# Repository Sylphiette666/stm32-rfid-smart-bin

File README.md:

# STM32与RFID积分式智能移动垃圾桶

嵌入式与RFID双课设的设计和实施资料。当前制作路线为**A1：单台低成本、复用已购模块和直插件，100×100mm裸PCB自行焊接**。主控为STM32F103C8T6，MCP23017成品扩展模块继续外置；一块PCB替代原PWR与IO两块洞洞板，模块按信号名接线。

## 从这里开始

1. [下载图解增强版Word手册](docs/manual/STM32%E4%B8%8ERFID%E6%99%BA%E8%83%BD%E7%A7%BB%E5%8A%A8%E5%9E%83%E5%9C%BE%E6%A1%B6_%E9%80%90%E6%AD%A5%E7%BB%84%E8%A3%85%E4%B8%8E%E8%B0%83%E8%AF%95%E5%AE%9E%E6%96%BD%E6%89%8B%E5%86%8C_%E5%9B%BE%E8%A7%A3%E5%A2%9E%E5%BC%BA%E7%89%88.docx)：保留330个步骤、33项功能；第62章为木板/PVC裁剪图，第63章和图45—49为当前A1 PCB、板外供电、模块接口及条件适配补充。第64章新增四套技能审查结论与接地加强后的调试要求。SG90与历史洞洞板图仍保留。[原版手册](docs/manual/STM32%E4%B8%8ERFID%E6%99%BA%E8%83%BD%E7%A7%BB%E5%8A%A8%E5%9E%83%E5%9C%BE%E6%A1%B6_%E9%80%90%E6%AD%A5%E7%BB%84%E8%A3%85%E4%B8%8E%E8%B0%83%E8%AF%95%E5%AE%9E%E6%96%BD%E6%89%8B%E5%86%8C.docx)保留。
2. [在线阅读全部步骤](docs/manual/ASSEMBLY.md)：按顺序检查、装配和调试，原330步不重编；图解以同名Word最新版为准。
3. [查看当前A1 PCB资料](hardware/current-low-cost/pcb-a/README.md)、[接线说明](hardware/current-low-cost/WIRING.md)、[逐针接口表](hardware/current-low-cost/pcb-a/connector-map.csv)、[BOM](hardware/current-low-cost/pcb-a/manufacturing/bom.csv)和[33项功能验收清单](docs/ACCEPTANCE.md)。裸板制造文件为[Gerber_RS274X.zip](hardware/current-low-cost/pcb-a/manufacturing/Gerber_RS274X.zip)，原理图及工程在[kicad目录](hardware/current-low-cost/pcb-a/kicad/)。
4. [查看SG90等图解与说明](docs/manual/illustrated-additions-20261010/)和[木板与PVC裁剪图解](docs/manual/cutting-diagrams-20261010/)；[旧PWR/IO洞洞板正反面与逐根焊线表](hardware/current-low-cost/perfboard/)仅作归档参考，不再作为A1 PCB施工接口。
5. [打开A1固件与调试说明](firmware/a1/README.md)：开发环境已确定为Keil，编译、下载及调试均在Keil完成，无需安装CubeMX、CubeIDE或CubeProgrammer。已提供工程和烧录文件；先按[实验室集中检查清单](firmware/a1/LAB_CHECKLIST.md)核对硬件，再逐模块上电调试。Word中旧软件路线以此说明和在线手册第37章为准。
6. 当前1号P2S继续昨天第二盘的上平台、舵机支架和喇叭圈。其余四台使用[底座带模块标牌版](hardware/mechanical/print-backup/labeled-bases-20261101/README.md)：两片底板仍可沿用，4/5号两盘精细附件更新为带标牌版，约5小时17分/5小时34分；新增任务同时开打约5小时34分完成，共387g PLA。11个待打印底座加名称，上盖和活动件保持；同名Word66.9节及图解63为当前说明。已切片，未实物试装。

本次接地加强版新增55个GND过孔，不增加元件采购或手焊任务；裸板制造检查通过，仍保留EMC及实物验证边界。详见[四套技能联合审查报告](hardware/current-low-cost/pcb-a/review/four-skills/四套技能联合审查报告.md)。

## 目录

[查看成品外观概念图](docs/appearance/README.md)（合盖与开盖两种状态，非实物照片）。

| 目录 | 内容 |
| --- | --- |
| `docs/manual/` | 原版及最新同名图解增强版Word、330步阅读版、内容源与图解生成源 |
| `docs/manual/illustrated-additions-20261010/` | 本轮SG90等新增图解及整合说明 |
| `docs/manual/cutting-diagrams-20261010/` | 木板/PVC五幅裁剪图、图源、孔位说明及检查记录 |
| `docs/planning/` | 功能成本选型、33项功能机械设计及功能数据 |
| `docs/appearance/` | 成品外观概念图及生成说明 |
| `hardware/mechanical/print-backup/` | PLA整片轻量模型、原5mm厚板备选、P2S打印方向、STEP源和几何检查 |
| `hardware/current-low-cost/` | 当前A1方案的边界、接线说明与归档入口 |
| `hardware/current-low-cost/pcb-a/` | 100×100mm裸PCB、原理图、制造Gerber、BOM和逐针接口表 |
| `hardware/current-low-cost/perfboard/` | 归档：原PWR与IO两块洞洞板正反面、孔位、逐根焊线表及外接说明 |
| `hardware/archive/pcb-v2.1/` | 旧PCF8574方案的嘉立创工程、KiCad、Gerber、BOM和贴片坐标 |
| `firmware/a1/` | A1应用固件、Keil工程、四组主机C测试、发布文件和集中调试说明 |
| `firmware/legacy/` | 保留的STM32/CMSIS基础文件 |
| `archive/` | 较早手册、采购表及折叠内胆参考图 |

## 当前状态与版本边界

- 已整理设计、采购、装配、接线、软件实施步骤和验收方法；文档步骤不代表已完成实物验证。
- 2026-10-13已实现A1应用固件，并通过编译与主机模拟测试；**没有完成实物烧录、标定和整机验收**。默认关闭电机/舵机动作，硬件型号与极性须确认；使用方式见`firmware/a1/README.md`。
- A1继续使用MCP23017成品模块与原MCU功能映射，复用已购器件；AO3400A裸管仍须焊转接板。新PCB只有JP3—JP10共8组跳帽，没有JP1/JP2。旧洞洞板接口及PCF8574 V2.1 PCB均不能混用。
- 当前电气制作基线为2026年10月12日A1 PCB补充；原330步的功能、机械装配和验收顺序保留。PCB的设计检查及制造文件不等于实物焊接、通电或33项功能验收已完成。
- 仓库内没有上传账户凭据、订单截图、渲染缓存、临时锁文件或工具依赖目录。

## 更新方式

后续每次增加图解，都加入同名图解增强版Word，更新目录并渲染检查排版，再替换本地与仓库中的同名版本；同步相关接线说明、图片和校验清单后，提交并推送到本仓库。原330个步骤保持编号。实测记录请写日期、硬件版本、固件提交号、测试条件和结果；未完成检查或实测的项目不能写成已完成。

初始归档日期：2026-10-10。文件校验值见[MANIFEST.sha256](MANIFEST.sha256)。第三方资料说明见[THIRD_PARTY.md](THIRD_PARTY.md)。

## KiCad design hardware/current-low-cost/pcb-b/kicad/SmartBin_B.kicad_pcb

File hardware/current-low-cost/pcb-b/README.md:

# SmartBin B1 模块线束 PCB

本版使用 KiCad，替代面包板和原洞洞板。现有 STM32 核心板、MCP23017、TB6612、降压/稳压板及传感器仍作为独立模块，通过现有排针和按信号标注的杜邦线连接。电池、电机、舵机和 DFPlayer 供电使用接线端子与合适线径，不通过细杜邦线。没有改变现有模块的排针焊接方向。

工程入口：`kicad/SmartBin_B.kicad_pro`；电路板：`kicad/SmartBin_B.kicad_pcb`；完整原理图：`checks/SmartBin_B_schematic.pdf`。B1 与旧 A1 的制造文件不能混用。

`mechanical/SmartBin_B.step` 是用于底座空间检查的PCB装配参考模型，包含KiCad库的名义元件外形；它不是现有独立模块的实测模型。其原点为元件面左上角，STEP中y轴与屏幕向下坐标相反。模型已检查为有效实体。

## 板形与新增电路

- 双层，125×100 mm，1.6 mm 厚，1 oz 铜。正面左上角为坐标原点，x 向右、y 向下。
- 四个 Ø3.2 mm 非金属化安装孔中心：(5,5)、(95,5)、(5,95)、(95,95) mm；孔距仍为 90×90 mm。板右侧比 A1 多出 25 mm，外形不再是 100×100 mm；一体打印底座须按此包络复核，不能按旧草图直接打印。
- 七颗 SN74LVC1G17DBVR（U2—U8，SOT-23-5）处理六路红外 DO 和 DFPlayer BUSY。缓冲器不反相，输入可接 3.3 V 或 5 V 逻辑信号，应用范围限定为共地、0—5.25 V。
- 每路 1 kΩ 输入串联、10 kΩ 上拉、100 nF 就地去耦；电阻和电容为 0805。七颗 IC 加二十一颗 0805 无源器件需要贴片焊接，其余器件以直插为主。
- 接 MCP 的缓冲器由 3V3_EXT 供电；接 PB8、PA12 的两路由 3V3_CORE 供电。两路 3.3 V 不并联。
- 原急停三管电路、AHCT125 输出提升、超声波 Echo 分压、电池 ADC、DHT 适配接口、灯驱动适配接口保留。

## 接口变化

完整逐针接线见 `connector-map.csv`，共 190 个端点。方焊盘为 1 脚；PCB 自定义针序不等于商品模块针序，按模块丝印逐根连接。

| 接口 | B1 接法 |
|---|---|
| J6 | 1=5V_BUS、2=GND，专供 DFPlayer VCC/GND；SPK1/SPK2 只接喇叭 |
| J31 | 1=GND、2=DF_RX、3=DF_BUSY_RAW；BUSY 经 U8 后到 MCP GPA6 |
| J33 | 1=3V3_EXT、2=5V_BUS、3=GND；4—9=IR0_RAW—IR5_RAW |
| J33 信号对应 | 4→GPB0、5→GPB1、6→GPB2、7→GPB3、8→PB8、9→PA12；信号功能沿用 A1 |
| J34 | 三脚均为 GND，分别连接 MCP 的 A0、A1、A2，使地址为 0x20 |
| J35 | 1=3V3_CORE、2=GND；低功耗辅助逻辑口 |
| J36 | 1=3V3_EXT、2=GND；低功耗辅助逻辑口 |
| J37 | 1=5V_BUS、2=GND；低功耗辅助逻辑口 |

J33 上的两种电源是供选择的独立脚，不能同时接到同一模块 VCC。模块 DO 可以进入对应 RAW 输入，不再需要为这七路另搭分压。其余传感器必须遵守各自接口电压，不能把“RAW 支持 5V”推广到所有 GPIO。

外置 AO3400A 转接模块仍接 J28；DHT 双向电平转换成品模块仍接 J23（按选用供电决定 JP8）。这两块应使用已焊好的小模块，不需要面包板。MCP 地址地使用 J34，模块电源按逐针表分配；需要分线时使用绝缘线束分支或现有接线端子。

## 焊接与检查

先焊 U2—U8 和 0805，再焊低矮直插件、排针、端子、电容、U1 插座。U2—U8 的 1 脚对准封装标记；U1 使用 SN74AHCT125N，不用 74HC125 代替。按 BOM 的 DNP 列保留可选电阻空位，不能把所有焊盘全部装满。

断电核查无焊桥、两路 3.3 V 不短接、极性正确。先单独调整降压至 5.0 V，再分阶段接入逻辑和模块；按既有手册确认跳帽供电选择。上拉默认使断线输入为高，感应有效电平和断线行为仍要逐项核对。不同模块断电时不要继续从外部给其信号脚送电。

架空车轮验证急停、释放后不自动续跑，然后再接舵机和负载。原急停只关闭轮电机驱动，并不切断舵机电源；外部 3.3 V 失电时的硬件联锁能力沿用 A1 的限制。本版未实焊、未带载、未做温升或 EMC 验证。

## 校验与制造

`checks/` 保存 ERC、DRC、实际导出网表及 372 个连接管脚/8 个 NC 的逐脚核对。`review/design-audit.json` 核对改动端点、缓冲器原厂引脚、安装孔和原 33 段粗电源线。制造输出只有在最终检查通过后才打包为 `manufacturing/Gerber_RS274X.zip`；BOM 在同目录。

规则：0.20 mm 间距，常规信号 0.30 mm、局部 0.25 mm，过孔 0.8/0.4 mm，原动力主干 3 mm/分支 2 mm保留。低电流缓冲器供电脚采用短 0.30 mm 扇出连接本地去耦，不用于动力供电。双层板的局部回流绕行和原 C8 距离限制仍需实物验证；数字 DRC 通过不等于抗干扰认证。

使用的技能与资料：[mash KiCad skills](https://github.com/mash/kicad-skills)、[PCB-design 检查流程](https://github.com/Toaster496/PCB-design)、[TI SN74LVC1G17 数据手册](https://www.ti.com/lit/ds/symlink/sn74lvc1g17.pdf)。用户已改用 KiCad，本版没有执行 EasyEDA 检查。

## 舵机接线示意图

`diagrams/servo/servo_wiring.png`（同目录另有 A4 横向 `servo_wiring_A4.pdf`）给出 SG90 三根线的分工：红→`J5.1`（5V_BUS，22 AWG，主电流只走这一路）、棕/黑→`J5.2`（GND）、橙→`J20.1`（SERVO_SIG_5V，由 `U1 SN74AHCT125N` 把 PA0 的 3.3 V PWM 提升到 5 V，`R6` 10 kΩ 下拉）。原厂 3 芯延长线必须在配电处拆成电源、信号两路，整根插 `J20` 会把 5 V 灌进信号排针。图源 `diagrams/servo/build_servo_diagram.py`，数据来源与自检见同目录 `diagram-manifest.json`、`diagram-qa.json`（排版自检 0 重叠、导线 0 交叉、像素抽查通过）。该图是接线图，未做实物通电验证。

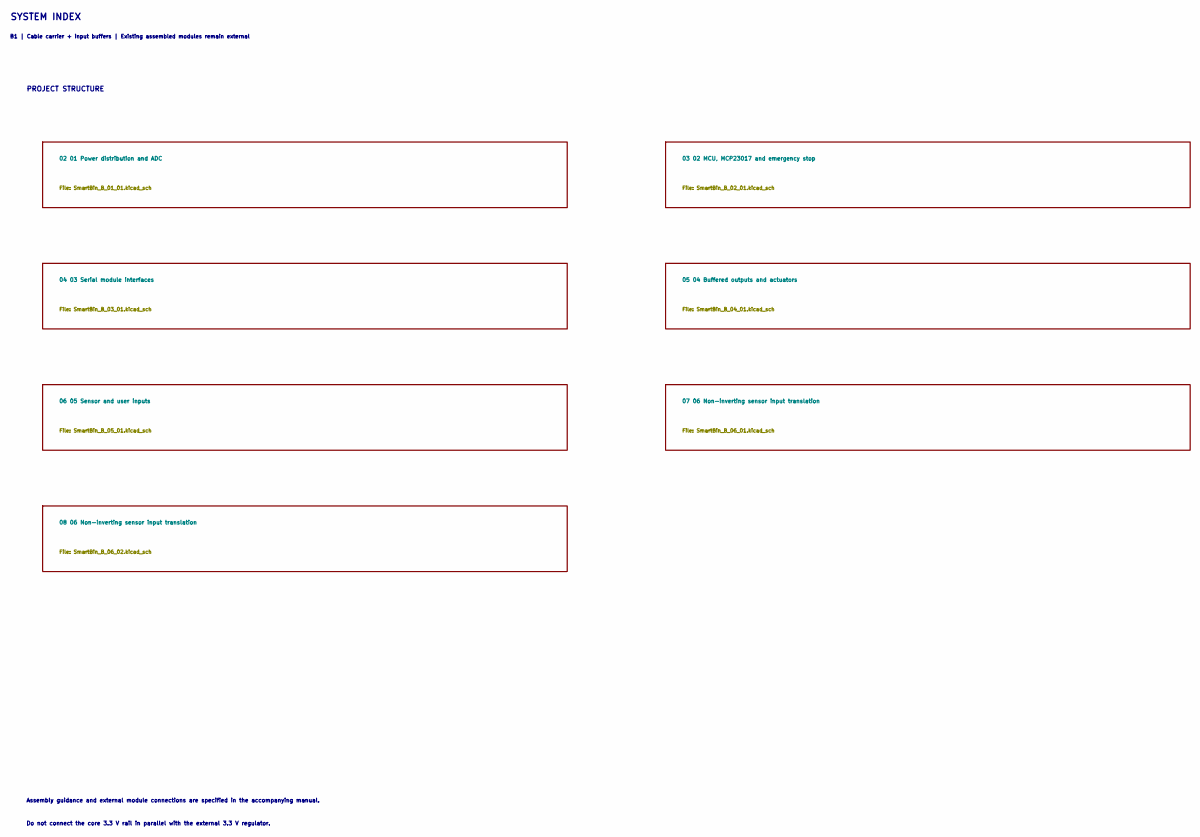
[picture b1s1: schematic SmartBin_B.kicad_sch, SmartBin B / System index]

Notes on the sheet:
SYSTEM INDEX
B1 | Cable carrier + input buffers | Existing assembled modules remain external
PROJECT STRUCTURE
Assembly guidance and external module connections are specified in the accompanying manual.
Do not connect the core 3.3 V rail in parallel with the external 3.3 V regulator.

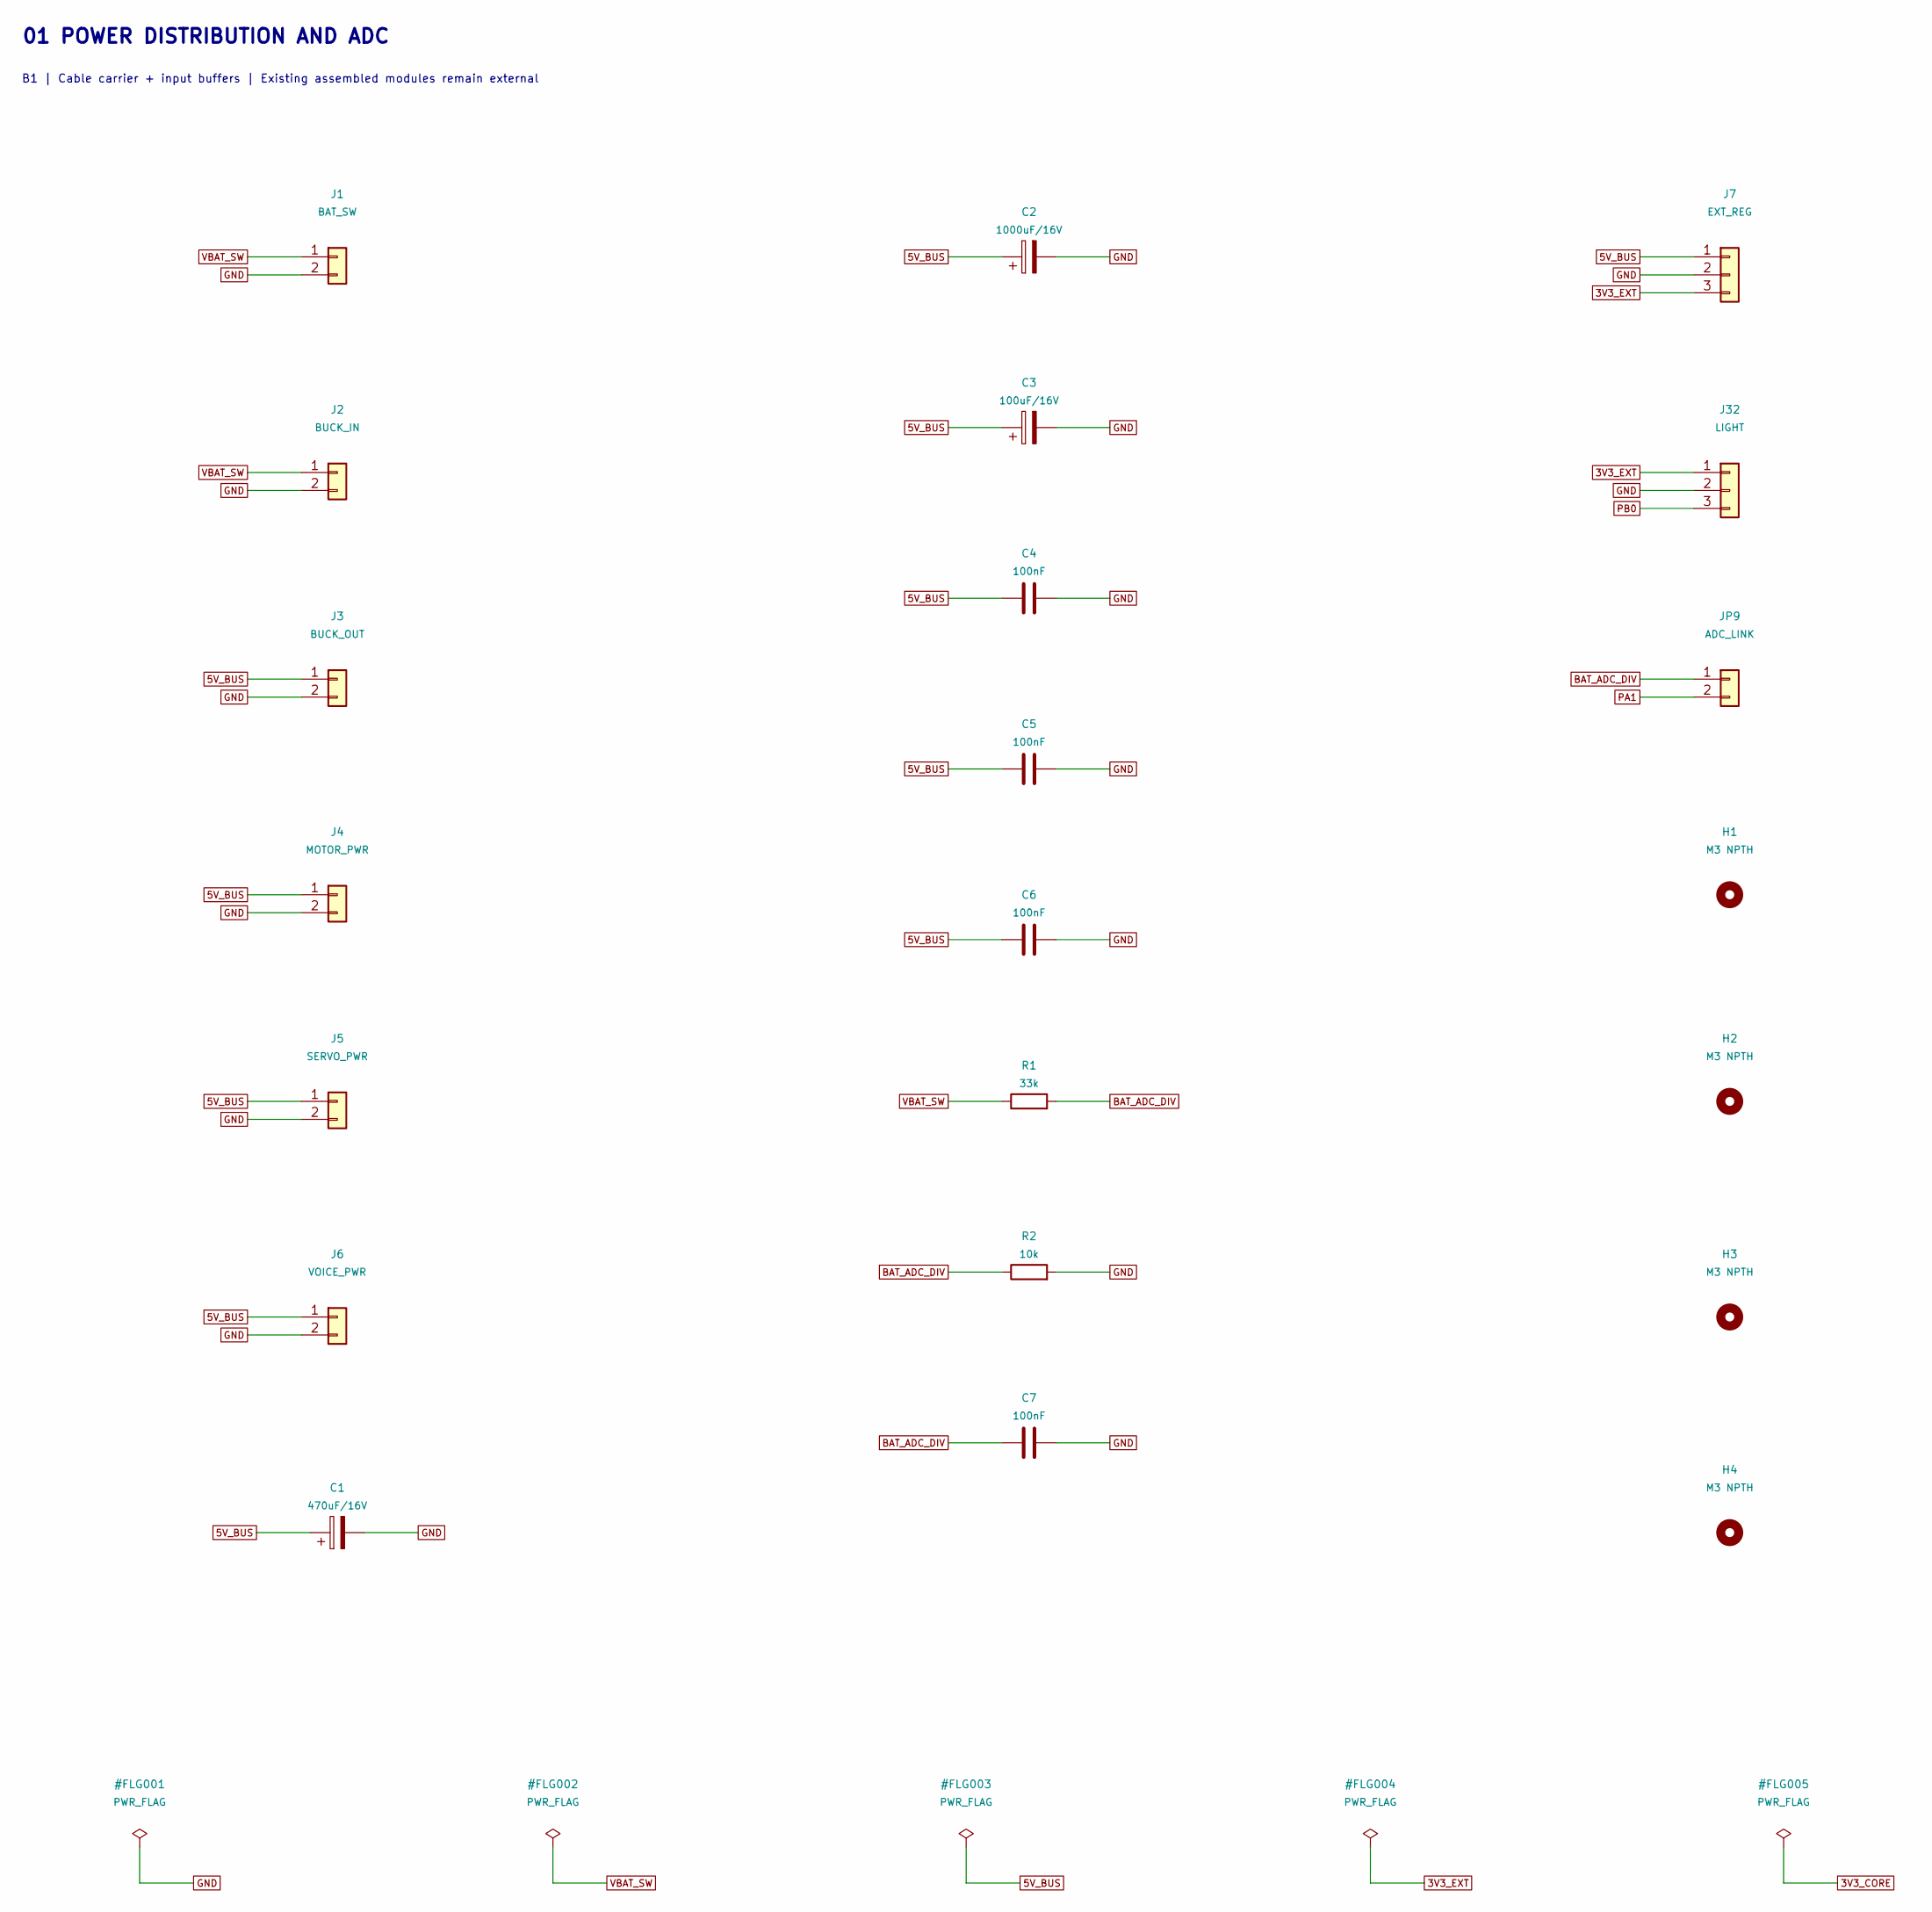
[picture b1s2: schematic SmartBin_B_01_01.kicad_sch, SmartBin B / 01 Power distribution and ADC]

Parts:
C1: 470uF/16V; CP_Radial_D12.5mm_P5.00mm
C2: 1000uF/16V; CP_Radial_D12.5mm_P5.00mm
C3: 100uF/16V; CP_Radial_D12.5mm_P5.00mm
C4, C5, C6, C7: 100nF; C_Disc_D5.0mm_W2.5mm_P5.00mm
H1, H2, H3, H4: M3 NPTH; MountingHole_3.2mm_M3
J1: BAT_SW; TerminalBlock_Phoenix_MKDS-1,5-2-5.08_1x02_P5.08mm_Horizont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
J2: BUCK_IN; TerminalBlock_Phoenix_MKDS-1,5-2-5.08_1x02_P5.08mm_Horizont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
J3: BUCK_OUT; TerminalBlock_Phoenix_MKDS-1,5-2-5.08_1x02_P5.08mm_Horizont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
J4: MOTOR_PWR; TerminalBlock_Phoenix_MKDS-1,5-2-5.08_1x02_P5.08mm_Horizont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
J5: SERVO_PWR; TerminalBlock_Phoenix_MKDS-1,5-2-5.08_1x02_P5.08mm_Horizont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
J6: VOICE_PWR; TerminalBlock_Phoenix_MKDS-1,5-2-5.08_1x02_P5.08mm_Horizont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
J7: EXT_REG; PinHeader_1x03_P2.54mm_Vertical
J32: LIGHT; PinHeader_1x03_P2.54mm_Vertical
JP9: ADC_LINK; PinHeader_1x02_P2.54mm_Vertical
R1: 33k; R_Axial_DIN0207_L6.3mm_D2.5mm_P10.16mm_Horizontal
R2: 10k; R_Axial_DIN0207_L6.3mm_D2.5mm_P10.16mm_Horizontal

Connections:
3V3_EXT: J7.3, J32.1; also elsewhere on the board
5V_BUS: C1.1, C2.1, C3.1, C4.1, C5.1, C6.1, J3.1, J4.1, J5.1, J6.1, J7.1; also elsewhere on the board
BAT_ADC_DIV: C7.1, JP9.1, R1.2, R2.1
GND: C1.2, C2.2, C3.2, C4.2, C5.2, C6.2, C7.2, J1.2, J2.2, J3.2, J4.2, J5.2, J6.2, J7.2, J32.2, R2.2; also elsewhere on the board
PA1: JP9.2; also elsewhere on the board
PB0: J32.3; also elsewhere on the board
VBAT_SW: J1.1, J2.1, R1.1; also elsewhere on the board

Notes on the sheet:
01 POWER DISTRIBUTION AND ADC
B1 | Cable carrier + input buffers | Existing assembled modules remain external

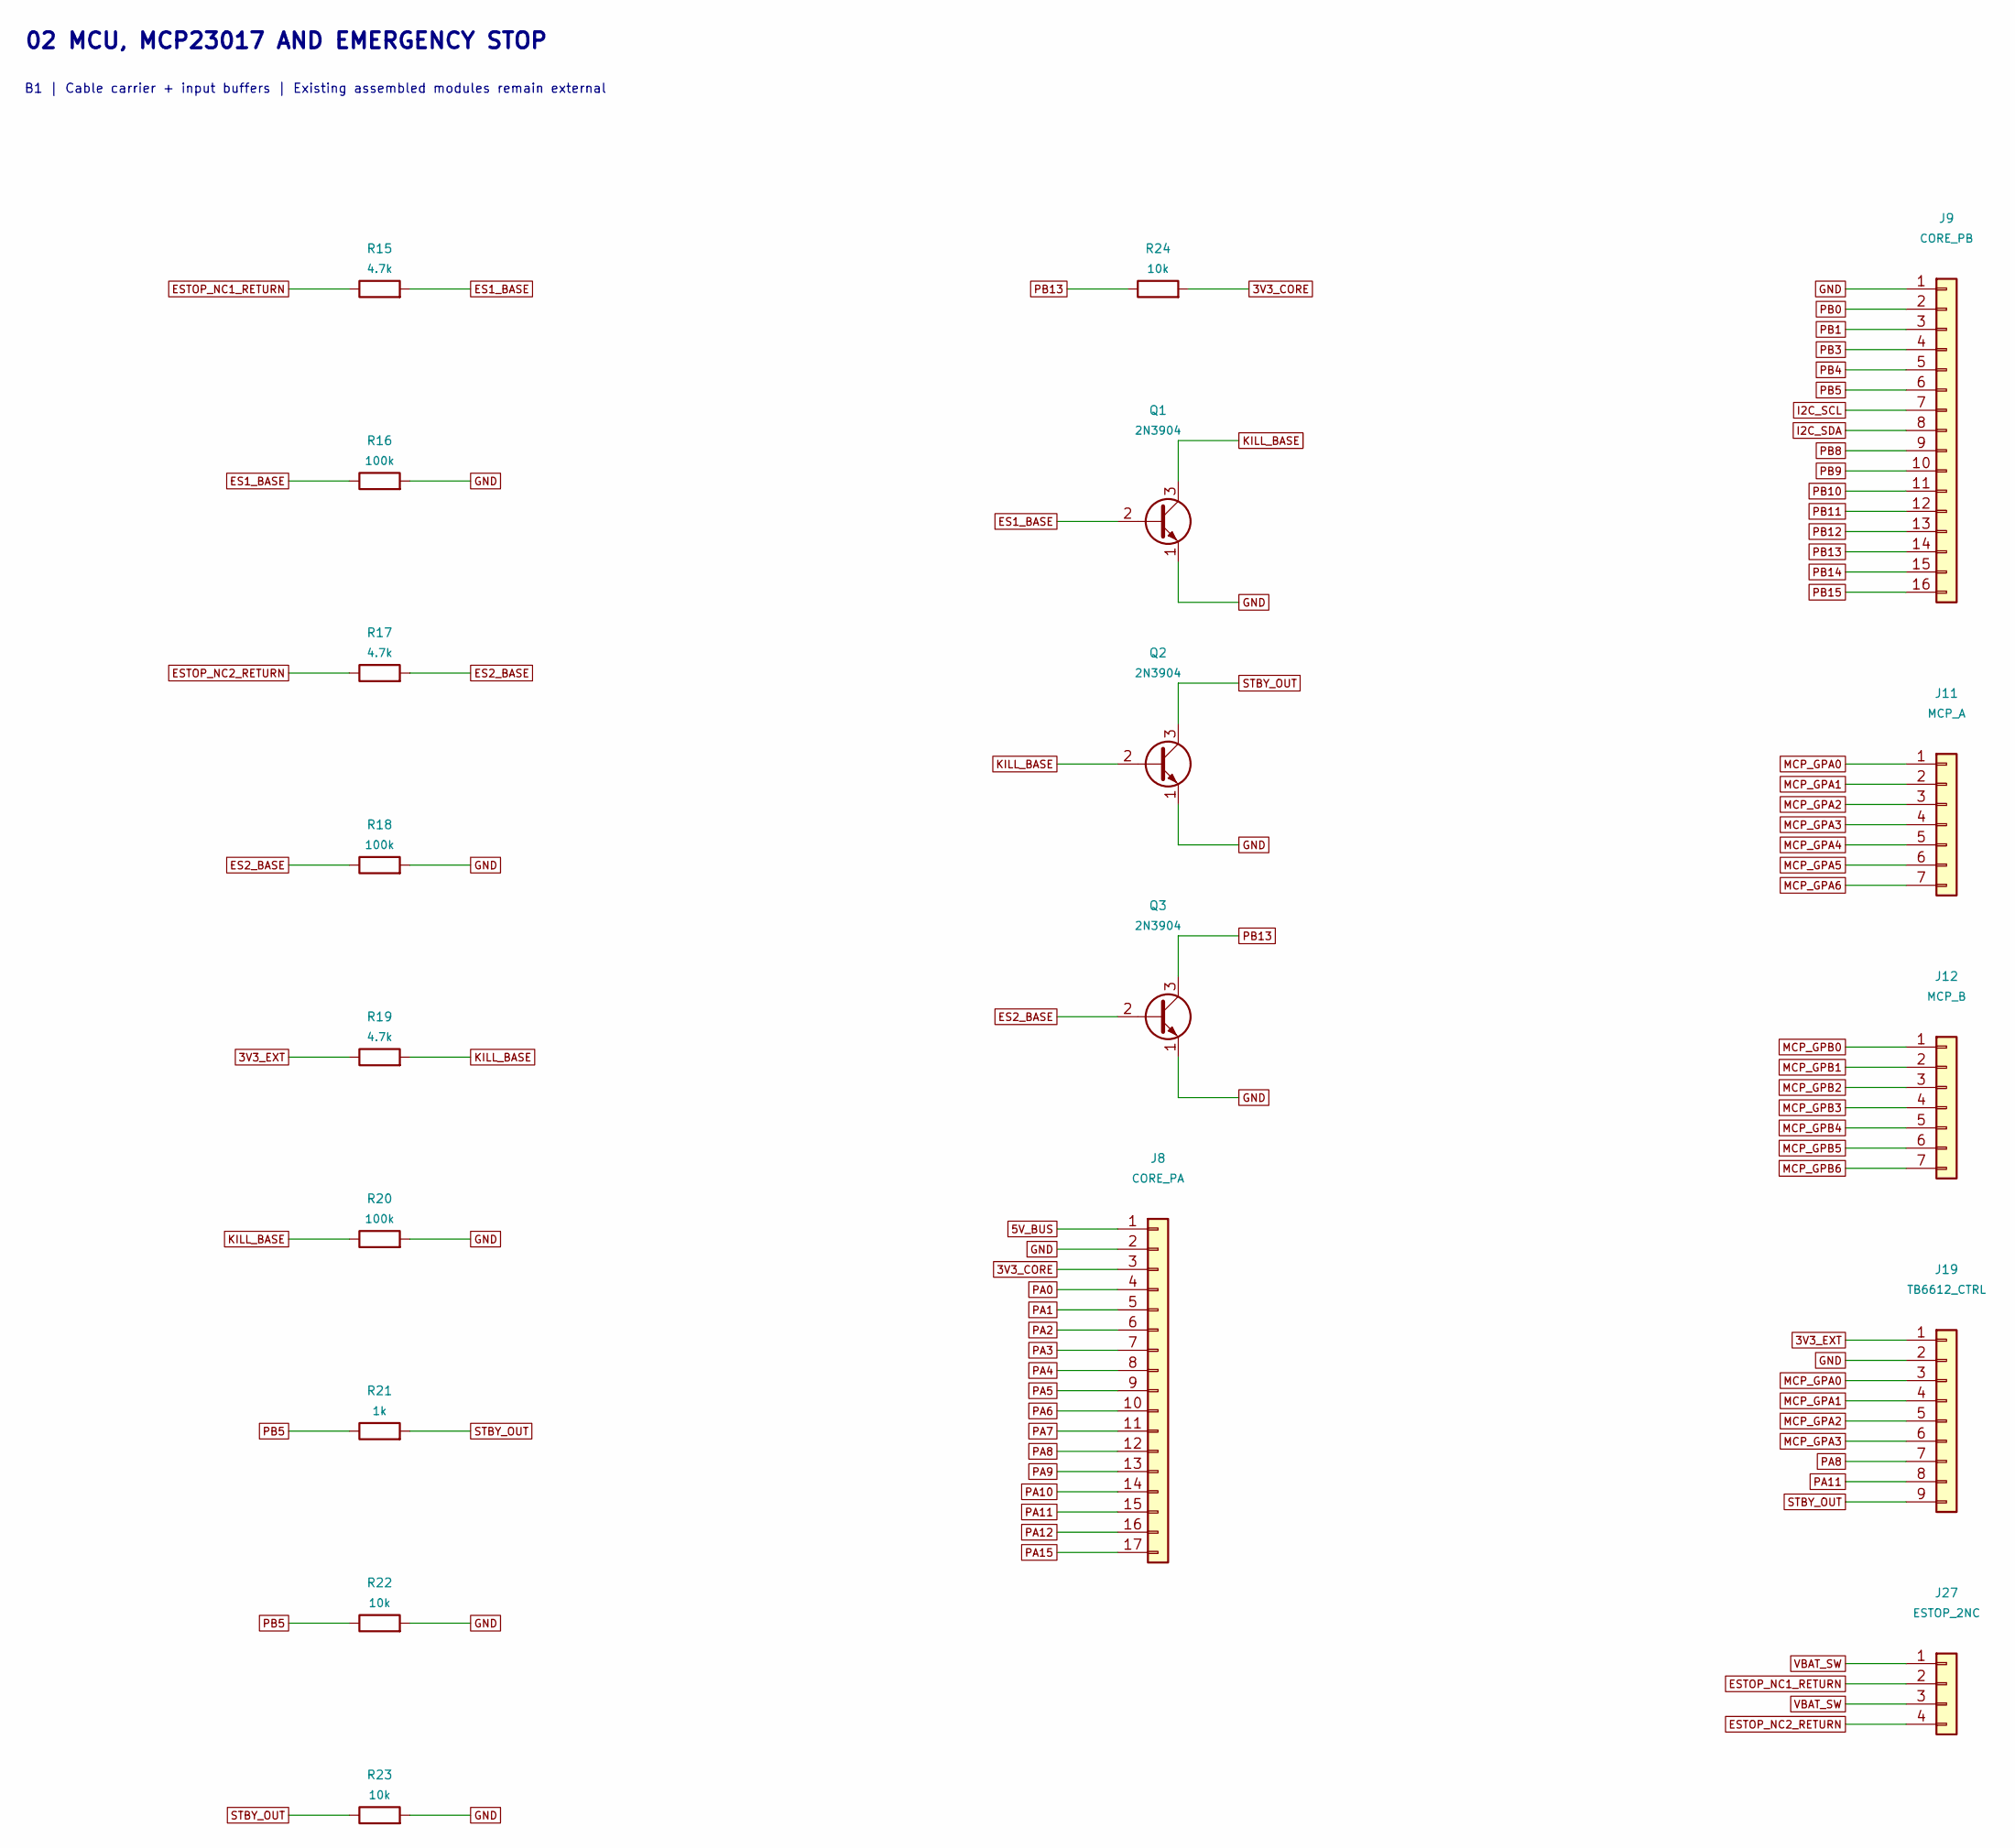
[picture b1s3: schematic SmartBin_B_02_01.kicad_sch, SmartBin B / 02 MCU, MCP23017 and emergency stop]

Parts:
J8: CORE_PA; PinHeader_1x17_P2.54mm_Vertical
J9: CORE_PB; PinHeader_1x16_P2.54mm_Vertical
J11: MCP_A; PinHeader_1x07_P2.54mm_Vertical
J12: MCP_B; PinHeader_1x07_P2.54mm_Vertical
J19: TB6612_CTRL; PinHeader_1x09_P2.54mm_Vertical
J27: ESTOP_2NC; PinHeader_1x04_P2.54mm_Vertical
Q1, Q2, Q3: 2N3904; TO-92_Inline_Wide
R15, R17, R19: 4.7k; R_Axial_DIN0207_L6.3mm_D2.5mm_P10.16mm_Horizontal
R16, R18, R20: 100k; R_Axial_DIN0207_L6.3mm_D2.5mm_P10.16mm_Horizontal
R21: 1k; R_Axial_DIN0207_L6.3mm_D2.5mm_P10.16mm_Horizontal
R22, R23, R24: 10k; R_Axial_DIN0207_L6.3mm_D2.5mm_P10.16mm_Horizontal

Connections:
3V3_CORE: J8.3, R24.2; also elsewhere on the board
3V3_EXT: J19.1, R19.1; also elsewhere on the board
5V_BUS: J8.1; also elsewhere on the board
ES1_BASE: Q1.2 (B), R15.2, R16.1
ES2_BASE: Q3.2 (B), R17.2, R18.1
ESTOP_NC1_RETURN: J27.2, R15.1
ESTOP_NC2_RETURN: J27.4, R17.1
GND: J8.2, J9.1, J19.2, Q1.1 (E), Q2.1 (E), Q3.1 (E), R16.2, R18.2, R20.2, R22.2, R23.2; also elsewhere on the board
I2C_SCL: J9.7; also elsewhere on the board
I2C_SDA: J9.8; also elsewhere on the board
KILL_BASE: Q1.3 (C), Q2.2 (B), R19.2, R20.1
MCP_GPA0: J11.1, J19.3
MCP_GPA1: J11.2, J19.4
MCP_GPA2: J11.3, J19.5
MCP_GPA3: J11.4, J19.6
MCP_GPA4: J11.5; also elsewhere on the board
MCP_GPA5: J11.6; also elsewhere on the board
MCP_GPA6: J11.7; also elsewhere on the board
MCP_GPB0: J12.1; also elsewhere on the board
MCP_GPB1: J12.2; also elsewhere on the board
MCP_GPB2: J12.3; also elsewhere on the board
MCP_GPB3: J12.4; also elsewhere on the board
MCP_GPB4: J12.5; also elsewhere on the board
MCP_GPB5: J12.6; also elsewhere on the board
MCP_GPB6: J12.7; also elsewhere on the board
PA0: J8.4; also elsewhere on the board
PA1: J8.5; also elsewhere on the board
PA2: J8.6; also elsewhere on the board
PA3: J8.7; also elsewhere on the board
PA4: J8.8; also elsewhere on the board
PA5: J8.9; also elsewhere on the board
PA6: J8.10; also elsewhere on the board
PA7: J8.11; also elsewhere on the board
PA8: J8.12, J19.7
PA9: J8.13; also elsewhere on the board
PA10: J8.14; also elsewhere on the board
PA11: J8.15, J19.8
PA12: J8.16; also elsewhere on the board
PA15: J8.17; also elsewhere on the board
PB0: J9.2; also elsewhere on the board
PB1: J9.3; also elsewhere on the board
PB3: J9.4; also elsewhere on the board
PB4: J9.5; also elsewhere on the board
PB5: J9.6, R21.1, R22.1
PB8: J9.9; also elsewhere on the board
PB9: J9.10; also elsewhere on the board
PB10: J9.11; also elsewhere on the board
PB11: J9.12; also elsewhere on the board
PB12: J9.13; also elsewhere on the board
PB13: J9.14, Q3.3 (C), R24.1
PB14: J9.15; also elsewhere on the board
PB15: J9.16; also elsewhere on the board
STBY_OUT: J19.9, Q2.3 (C), R21.2, R23.1
VBAT_SW: J27.1, J27.3; also elsewhere on the board

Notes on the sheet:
02 MCU, MCP23017 AND EMERGENCY STOP
B1 | Cable carrier + input buffers | Existing assembled modules remain external

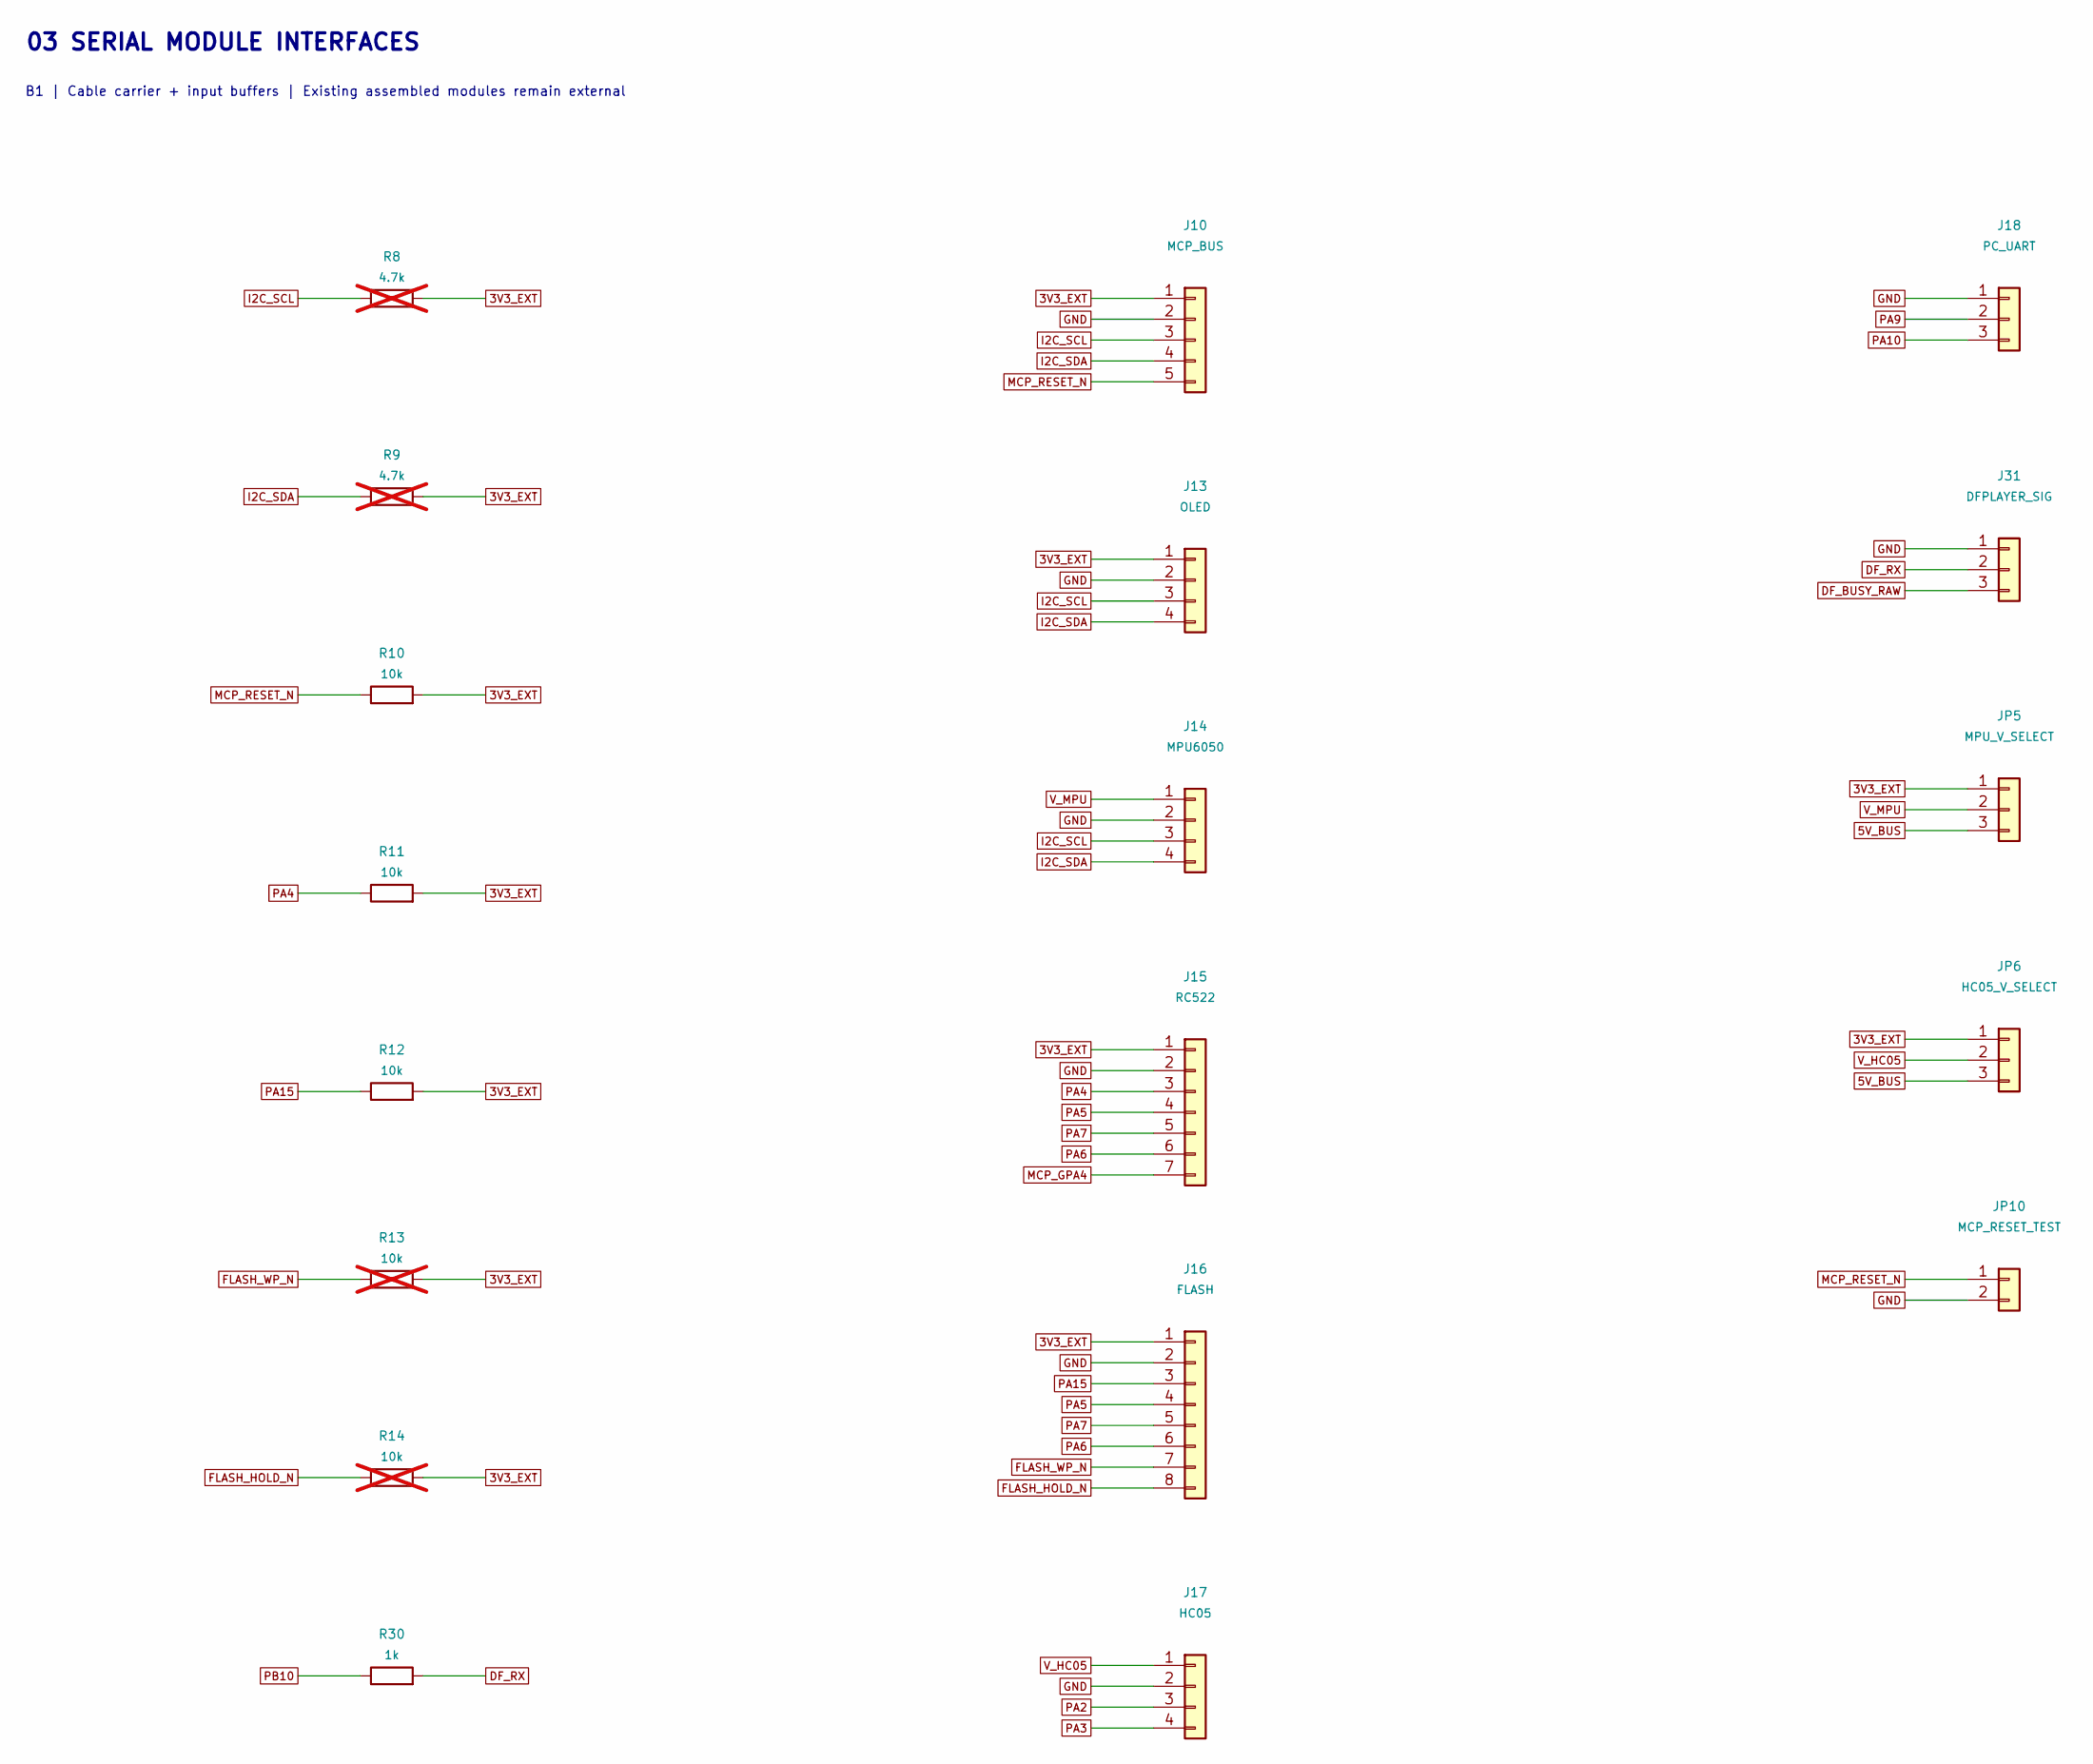
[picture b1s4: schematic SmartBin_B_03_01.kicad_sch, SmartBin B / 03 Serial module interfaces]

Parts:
J10: MCP_BUS; PinHeader_1x05_P2.54mm_Vertical
J13: OLED; PinHeader_1x04_P2.54mm_Vertical
J14: MPU6050; PinHeader_1x04_P2.54mm_Vertical
J15: RC522; PinHeader_1x07_P2.54mm_Vertical
J16: FLASH; PinHeader_1x08_P2.54mm_Vertical
J17: HC05; PinHeader_1x04_P2.54mm_Vertical
J18: PC_UART; PinHeader_1x03_P2.54mm_Vertical
J31: DFPLAYER_SIG; PinHeader_1x03_P2.54mm_Vertical
JP5: MPU_V_SELECT; PinHeader_1x03_P2.54mm_Vertical
JP6: HC05_V_SELECT; PinHeader_1x03_P2.54mm_Vertical
JP10: MCP_RESET_TEST; PinHeader_1x02_P2.54mm_Vertical
R8, R9: 4.7k; R_Axial_DIN0207_L6.3mm_D2.5mm_P10.16mm_Horizontal; not fitted
R10, R11, R12: 10k; R_Axial_DIN0207_L6.3mm_D2.5mm_P10.16mm_Horizontal
R13, R14: 10k; R_Axial_DIN0207_L6.3mm_D2.5mm_P10.16mm_Horizontal; not fitted
R30: 1k; R_Axial_DIN0207_L6.3mm_D2.5mm_P10.16mm_Horizontal

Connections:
3V3_EXT: J10.1, J13.1, J15.1, J16.1, JP5.1, JP6.1, R8.2, R9.2, R10.2, R11.2, R12.2, R13.2, R14.2; also elsewhere on the board
5V_BUS: JP5.3, JP6.3; also elsewhere on the board
DF_BUSY_RAW: J31.3; also elsewhere on the board
DF_RX: J31.2, R30.2
FLASH_HOLD_N: J16.8, R14.1
FLASH_WP_N: J16.7, R13.1
GND: J10.2, J13.2, J14.2, J15.2, J16.2, J17.2, J18.1, J31.1, JP10.2; also elsewhere on the board
I2C_SCL: J10.3, J13.3, J14.3, R8.1; also elsewhere on the board
I2C_SDA: J10.4, J13.4, J14.4, R9.1; also elsewhere on the board
MCP_GPA4: J15.7; also elsewhere on the board
MCP_RESET_N: J10.5, JP10.1, R10.1
PA2: J17.3; also elsewhere on the board
PA3: J17.4; also elsewhere on the board
PA4: J15.3, R11.1; also elsewhere on the board
PA5: J15.4, J16.4; also elsewhere on the board
PA6: J15.6, J16.6; also elsewhere on the board
PA7: J15.5, J16.5; also elsewhere on the board
PA9: J18.2; also elsewhere on the board
PA10: J18.3; also elsewhere on the board
PA15: J16.3, R12.1; also elsewhere on the board
PB10: R30.1; also elsewhere on the board
V_HC05: J17.1, JP6.2
V_MPU: J14.1, JP5.2

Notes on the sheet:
03 SERIAL MODULE INTERFACES
B1 | Cable carrier + input buffers | Existing assembled modules remain external
